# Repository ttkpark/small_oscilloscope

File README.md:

# small_oscilloscope
480x272 small-but-full oscilloscope

## stpes to go

### 아날로그 회로
 - 오실로스코프 회로 방식 파악 필요
 - DSO138의 회로 구성을 확인

### 오실로스코프 UI
 - 제어점과 보여줄 점을 파악 필요
 - `사용자의 입력은 무엇이 되어야 하는가`
 - `오실로스코프의 아날로그 유닛에 대한 제어 범위는?`
 - `어느 점을 보여주어야 하는가`

 - 트리거 인식 : 샘플 내에서 level지점 통과 지점을 지점 정중앙으로 둔다.
 - 샘플링 후 트리거 인식이 아니라, 샘플링 하면서 트리거 인식하면 트리거 지점이 정중앙되도록 샘플 수집하고 마무리.
 - 즉 샘플링 -> 트리거 x, 트리거 -> 샘플링 o

## 전원
- 상시 전원 공급 Source : VBAT=2.7 ~ 4.2
- BAT 충전       : 5V -> VBAT=4.2 (TP4056)
- 배터리 승압 회로 : VBAT -> 5V    (EA2208)
- 양전압 생성 회로 : VBAT -> 12V   (EA2208)
- 음전압 생성 회로 : 12V -> -12V   (LM2576)
- 백라이트 회로    : VBAT -> 24V   (EA2208)
- 강하 회로       : 5V -> 3.3V    (5V->3.3V 전압 강하 보드)

## 구성요소
- 본체 중앙처리장치
   - 구성 부품 : ESP32-PICO-D4
   - 인터페이스 : GPIO, SPI, I2C, ADC, UART, DAC 제공

- GPIO 확장 칩 : CH423
   - 구성 부품 : CH423
   - 인터페이스 : 본체 인터페이스 I2C 사용
               입출력 GPIO IO0-7, 출력 GPIO OC0-15 제공

- 아날로그 어레이
   - 구성 부품 : 전압 강하 OP-AMP, 감쇠율 조절 FET 및 릴레이, AC/DC 선택 릴레이, TRIG 생성기
   - 인터페이스 : GPIO 확장 칩 OC0,OC2-6,OC8-11 사용
                본체 인터페이스 GPIO(GPIO9-10), ADC(GPIO34, GPIO4), DAC(GPIO25, GPIO26) 사용
- 그래픽
   - 구성 부품 : FT800Q-T, 480x272 Monitor
   - 인터페이스 : 본체 인터페이스 SPI, 본체 GPIO (GPIO27:INT) 사용

- 조작부
   - 구성 부품 : 버튼, ROTARY Encoder, LED
   - 인터페이스 : GPIO 확장 칩 IO0-5, OC12-15 사용

- 연결부
   - 구성 부품 : CH340, BOOT Mode selecting MOSFET
   - 인터페이스 : 본체 인터페이스 UART, 본체 GPIO 부팅 핀(GPIO0, EN) 사용

- 충전부
   - 구성 부품 : 배터리 및 TP4056
   - 인터페이스 : GPIO 확장 칩 IO6-7 사용

- 전원부
   - 구성 부품 : 레퍼런스 전압을 나누는 Voltage Divisor
   - 인터페이스 : 본체 ADC 레퍼런스 전압 포트(GPIO35-39)

# 핀맵
|position|name|usage|
|----|----|----|
|UART(TX=GPIO1,RX=GPIO3)|CH340|Interface; uploading & debugging port|
|I2C(CK=GPIO21,DA=GPIO22)|CH423s|Interface; controlls the MOSFETs|
|SPI(SCK=GPIO18,MISO=GPIO19,MOSI=GPIO23,SS=GPIO5)|FT800Q-T|Interface; graphical controller, speaker enabled, DE Mode|
|GPIO27|/INT|LCD FT800Q-T Interrupt Pin|

|GPIO12|RE1B|Digital Input; Rotary Encoder 1(Volt Div/Pos) B|
|GPIO13|RE1A|Digital Input; Rotary Encoder 1(Volt Div/Pos) A|
|GPIO14|RE0B|Digital Input; Rotray Encoder 0(Time Div/Pos) B|
|GPIO15|RE0A|Digital Input; Rotray Encoder 0(Time Div/Pos) A|

|GPIO9|TRIG0|Digital Input, interrupt; open-drain, LOW if TRIG<ADC0|
|GPIO10|TRIG1|Digital Input, interrupt; open-drain, LOW if TRIG<ADC1|
|GPIO25|TRIG|Analog Output;  Trigger Output(same level with ADC0,1 pin)|
|GPIO34|ADC0|Analog Input;  Channel 0 input|
|GPIO4|ADC1|Analog Input;  Channel 1 input|
|GPIO26|TESTPIN|1kHz Signal Output pin|

|GPIO35|VREF3V3|Analog Reference Input;  3V3(VDD) ref, Vin=V33/2|
|GPIO36|VREFBAT|Analog Reference Input;  VBAT ref, Vin=VBAT/2|
|GPIO37|VREF5V |Analog Reference Input;  5V ref, Vin=V5/4.333|
|GPIO38|VREF12V|Analog Reference Input;  12V ref,Vin=V12/6.732|
|GPIO39|VREF135|Analog Reference Input;  2.7V ref, Vin=1.35V |

|CH423s-IO0|RE0P|Input; Rotary Encoder 0 Pushbutton(LOW Active)|
|CH423s-IO1|RE1P|Input; Rotary Encoder 1 Pushbutton(LOW Active)|
|CH423s-IO2|SW0|Input; button 0(LOW ACTIVE)|
|CH423s-IO3|SW1|Input; button 1(LOW ACTIVE)|
|CH423s-IO4|SW2|Input; button 2(LOW ACTIVE)|
|CH423s-IO5|SW3|Input; button 3(LOW ACTIVE)|
|CH423s-IO6|STDBY|Input; BATTERY 충전 완료면 HIGH|
|CH423s-IO7|CHRG|Input; BATTERY 충전 중이면 HIGH|
|CH423s-OC0|Q1|Output; Line 0 DC input analog switch|
|CH423s-OC1|BACKLIGHT|Output; LCD BACKLIGHT|
|CH423s-OC2|Q3|Output; Line 0 1차 1/10 감쇠|
|CH423s-OC3|Q4|Output; Line 0 1차 1/100 감쇠|
|CH423s-OC4|Q5|Output; Line 0 2차 1/2 감쇠|
|CH423s-OC5|Q6|Output; Line 0 2차 1/5 감쇠|
|CH423s-OC6|Q7|Output; Line 1 DC input analog switch|
|CH423s-OC7|-|Output; -|
|CH423s-OC8|Q9|Output; Line 1 1차 1/10 감쇠|
|CH423s-OC9|Q10|Output; Line 1 1차 1/100 감쇠|
|CH423s-OC10|Q11|Output; Line 1 2차 1/2 감쇠|
|CH423s-OC11|Q12|Output; Line 1 2차 1/5 감쇠|
|CH423s-OC12|LED0|Output; GP LED (Red)|
|CH423s-OC13|LED1|Output; GP LED (Green)|
|CH423s-OC14|LEDRE0|Output; Rotary Encoder 0 LED (Green)|
|CH423s-OC15|LEDRE1|Output; Rotary Encoder 1 LED (Green)|

# 하드웨어 연결 및 기능 구조

## 본체 중앙처리장치
   - 구성 부품 : ESP32-PICO-D4
   - 인터페이스 : GPIO, SPI, I2C, ADC, UART, DAC 제공

## GPIO 확장 칩 : CH423
   - 구성 부품 : CH423
   - 인터페이스 : 본체 인터페이스 I2C 사용
               입출력 GPIO IO0-7, 출력 GPIO OC0-15 제공
### 인터페이스 상세
|position|name|usage|
|----|----|----|
|I2C(CK=GPIO21,DA=GPIO22)|CH423s|Interface; controlls the MOSFETs|

### 설정
- 주소는 0x20이다. (7-bit addr)
analog_test_simple.c:84 esp_err_t test_ch423_circuit_simple(uint8_t *read_data) 의 테스트 함수에서 초기화 및 읽고 쓰는 법에 대해 쓰여 있다.

## 아날로그 어레이
- 구성 부품 : 전압 강하 OP-AMP, 감쇠율 조절 FET 및 릴레이, AC/DC 선택 릴레이, TRIG 생성기
- 인터페이스 : GPIO 확장 칩 OC0,OC2-6,OC8-11 사용
             본체 인터페이스 GPIO(GPIO9-10), ADC(GPIO34, GPIO4), DAC(GPIO25, GPIO26) 사용
### 인터페이스 상세
|position|name|usage|
|----|----|----|
|GPIO9|TRIG0|Digital Input, interrupt; open-drain, LOW if TRIG<ADC0|
|GPIO10|TRIG1|Digital Input, interrupt; open-drain, LOW if TRIG<ADC1|
|GPIO25|TRIG|Analog Output;  Trigger Output(same level with ADC0,1 pin)|
|GPIO34|ADC0|Analog Input;  Channel 0 input|
|GPIO35|ADC1|Analog Input;  Channel 1 input|
|GPIO26|TESTPIN|1kHz Signal Output pin|

|CH423s-OC0|Q1|Output; Line 0 DC input analog switch|
|CH423s-OC2|Q3|Output; Line 0 1차 1/10 감쇠|
|CH423s-OC3|Q4|Output; Line 0 1차 1/100 감쇠|
|CH423s-OC4|Q5|Output; Line 0 2차 1/2 감쇠|
|CH423s-OC5|Q6|Output; Line 0 2차 1/5 감쇠|
|CH423s-OC6|Q7|Output; Line 1 DC input analog switch|
|CH423s-OC8|Q9|Output; Line 1 1차 1/10 감쇠|
|CH423s-OC9|Q10|Output; Line 1 1차 1/100 감쇠|
|CH423s-OC10|Q11|Output; Line 1 2차 1/2 감쇠|
|CH423s-OC11|Q12|Output; Line 1 2차 1/5 감쇠|

### 프로브부터 ADC 포트까지 감쇠 회로 및 전압의 관계
- [출력] - [AC/DC 선택]  -   [1차 감쇠 회로] - [2차 감쇠 회로] - 레벨 쉬프터

### 감쇠율 조정 로직 : AC/DC 선택
|Q1/Q7|상태|
|--|--|
|0|DC입력(원본)|
|1|AC입력(AC성분만)|

### 감쇠율 조정 로직 : 1차 감쇠기
|Q3/Q9|Q4/Q10|상태|
|--|--|alpha_1|
|0|0|1|
|0|1|1/100|
|1|0|1/10|
|1|1|INVALD|
- V1 = alpha_1 * Vi

### 감쇠율 조정 로직 : 2차 감쇠기
|Q5/Q11|Q6/Q12|상태|
|--|--|alpha_2|
|0|0|1|
|0|1|1/5|
|1|0|1/2|
|1|1|INVALD|
- V2 = alpha_2 * V1

### 레벨 쉬프터 식
- Vadc = 8 * V2 + (V12/7.2)

### 출력과 ADC 입력의 관계
- Vadc = 8 * alpha_2 * alpha_1 * Vi + (V12 / 7.2)
- alpha_2,alpha_1은 1차 2차 감쇠값, Vadc는 adc포트 전압, Vi는 프로브 전압, V12는 12V레인 전압

### 트리거
- TRIG0, TRIG1 핀은 pull-up되어야 한다.
|TRIG>ADCn|TRIGn|
|--|--|
|true|HIGH|
|false|LOW|

## 그래픽
   - 구성 부품 : FT800Q-T, 480x272 Monitor
   - 인터페이스 : 본체 인터페이스 SPI, 본체 GPIO (GPIO27:INT) 사용

|position|name|usage|
|----|----|----|
|SPI(SCK=GPIO18,MISO=GPIO19,MOSI=GPIO23,SS=GPIO5)|FT800Q-T|Interface; graphical controller, speaker enabled, DE Mode|
|GPIO27|/INT|LCD FT800Q-T Interrupt Pin|
|CH423s-OC1|BACKLIGHT|Output; LCD BACKLIGHT|
### 사용법
- 사전에 반드시 **CH423이 먼저 초기화되고, BACKLIGHT 핀을 LOW 해야 한다.**
- 아래 코드처럼 초기화하고, 그림을 그리고 효과음을 낸다.
```c
   // FT800 초기화
    if (!initFT800()) {
        ESP_LOGI(TAG, "FT800 test passed");
    } else {
        ESP_LOGE(TAG, "FT800 test failed");
    }
    vTaskDelay(pdMS_TO_TICKS(1000));

    spi_speedup();
    
    // FT800 사용
	 clrscr();
    while(1){
		static uint32_t frames = 0;
        uint32_t frames_old = frames;
        frames = HOST_MEM_RD32(REG_FRAMES);
        if(frames_old != frames)
        {
            lcd_start_screen(frames);
            //ESP_LOGI(TAG, "FRAMES: %ld", frames);

            char str[100];
            sprintf(str, "FRAMES: %ld", frames);
            cmd(COLOR_RGB(0xDE,0xDE,0xDE));
            cmd_text(10,230, 27,0, str);
            
            memset(str, 0, sizeof(str));
            sprintf(str, "GPIO12 = %d", gpio_get_level(12));
            cmd(COLOR_RGB(0xDE,0xDE,0xDE));
            cmd_text(470,230, 26,OPT_RIGHTX, str);

            cmd(DISPLAY());
            cmd(CMD_SWAP);	
        }
        vTaskDelay(pdMS_TO_TICKS(1));
    }

    // 소리 내기
   HOST_MEM_WR8(REG_VOL_SOUND, 0xFF);      	
   switch((frames%180)/60){
      case 0:
         HOST_MEM_WR16(REG_SOUND, 0x50);     
         break;
      case 1:
         HOST_MEM_WR16(REG_SOUND, 0x51);
         break;
      case 2:
         HOST_MEM_WR16(REG_SOUND, 0x56);
         break;
   }
   HOST_MEM_WR8(REG_PLAY, 1); 
   
```

## 조작부
   - 구성 부품 : 버튼, ROTARY Encoder, LED
   - 인터페이스 : GPIO 확장 칩 IO0-5, OC12-15 사용

|position|name|usage|
|----|----|----|
|GPIO12|RE1B|Digital Input; Rotary Encoder 1(Volt Div/Pos) B|
|GPIO13|RE1A|Digital Input; Rotary Encoder 1(Volt Div/Pos) A|
|GPIO14|RE0B|Digital Input; Rotray Encoder 0(Time Div/Pos) B|
|GPIO15|RE0A|Digital Input; Rotray Encoder 0(Time Div/Pos) A|
|CH423s-IO0|RE0P|Input; Rotary Encoder 0 Pushbutton(LOW Active)|
|CH423s-IO1|RE1P|Input; Rotary Encoder 1 Pushbutton(LOW Active)|
|CH423s-IO2|SW0|Input; button 0(LOW ACTIVE)|
|CH423s-IO3|SW1|Input; button 1(LOW ACTIVE)|
|CH423s-IO4|SW2|Input; button 2(LOW ACTIVE)|
|CH423s-IO5|SW3|Input; button 3(LOW ACTIVE)|
|CH423s-OC12|LED0|Output; GP LED (Red)|
|CH423s-OC13|LED1|Output; GP LED (Green)|
|CH423s-OC14|LEDRE0|Output; Rotary Encoder 0 LED (Green)|
|CH423s-OC15|LEDRE1|Output; Rotary Encoder 1 LED (Green)|

- 로터리 스위치의 움직임 방향, 버튼의 눌림을 알 수 있고, LED 4개로 확인할 수 있다.

## 연결부
   - 구성 부품 : CH340, BOOT Mode selecting MOSFET
   - 인터페이스 : 본체 인터페이스 UART, 본체 GPIO 부팅 핀(GPIO0, EN) 사용

|position|name|usage|
|----|----|----|
|UART(TX=GPIO1,RX=GPIO3)|CH340|Interface; uploading & debugging port|

## 충전부
   - 구성 부품 : 배터리 및 TP4056
   - 인터페이스 : GPIO 확장 칩 IO6-7 사용
|position|name|usage|
|----|----|----|
|CH423s-IO6|STDBY|Input; BATTERY 충전 완료면 HIGH|
|CH423s-IO7|CHRG|Input; BATTERY 충전 중이면 HIGH|

### 충전 상태 설명
|STDBY|CHRG|상태|
|--|--|--|
|LOW |LOW |외부전원 분리됨|
|LOW |HIGH|충전 중|
|HIGH|LOW |충전 완료|
|HIGH|HIGH|INVALID, 아마도 충전중|

## 전원부
   - 구성 부품 : 레퍼런스 전압을 나누는 Voltage Divisor
   - 인터페이스 : 본체 ADC 레퍼런스 전압 포트(GPIO35-39)

### 인터페이스 상세
|position|name|usage|
|----|----|----|
|GPIO36|VREFBAT|Analog Reference Input;  VBAT ref, Vin=VBAT/2|
|GPIO37|VREF5V |Analog Reference Input;  5V ref, Vin=V5/4.333|
|GPIO38|VREF12V|Analog Reference Input;  12V ref,Vin=V12/6.732|
|GPIO39|VREF135|Analog Reference Input;  2.7V ref, Vin=1.35V |

### 사용법
- VREF135 포트는 제너 다이오드로 연결된 거의 신뢰성 있는 전압이다. 이것을 기준으로 ADC Max Volt를 역산한다.(=VDD)
- VREFBAT의 입력을 전압으로 변환해 배터리 전압을 추출한다.
- VREF5V, 12V의 ADC입력을 전압으로 변환해 각 레인의 전압을 추출한다.
- VREF3V3은 VDD로 계산되지만, 검증용으로 예비로 전압을 추출한다.

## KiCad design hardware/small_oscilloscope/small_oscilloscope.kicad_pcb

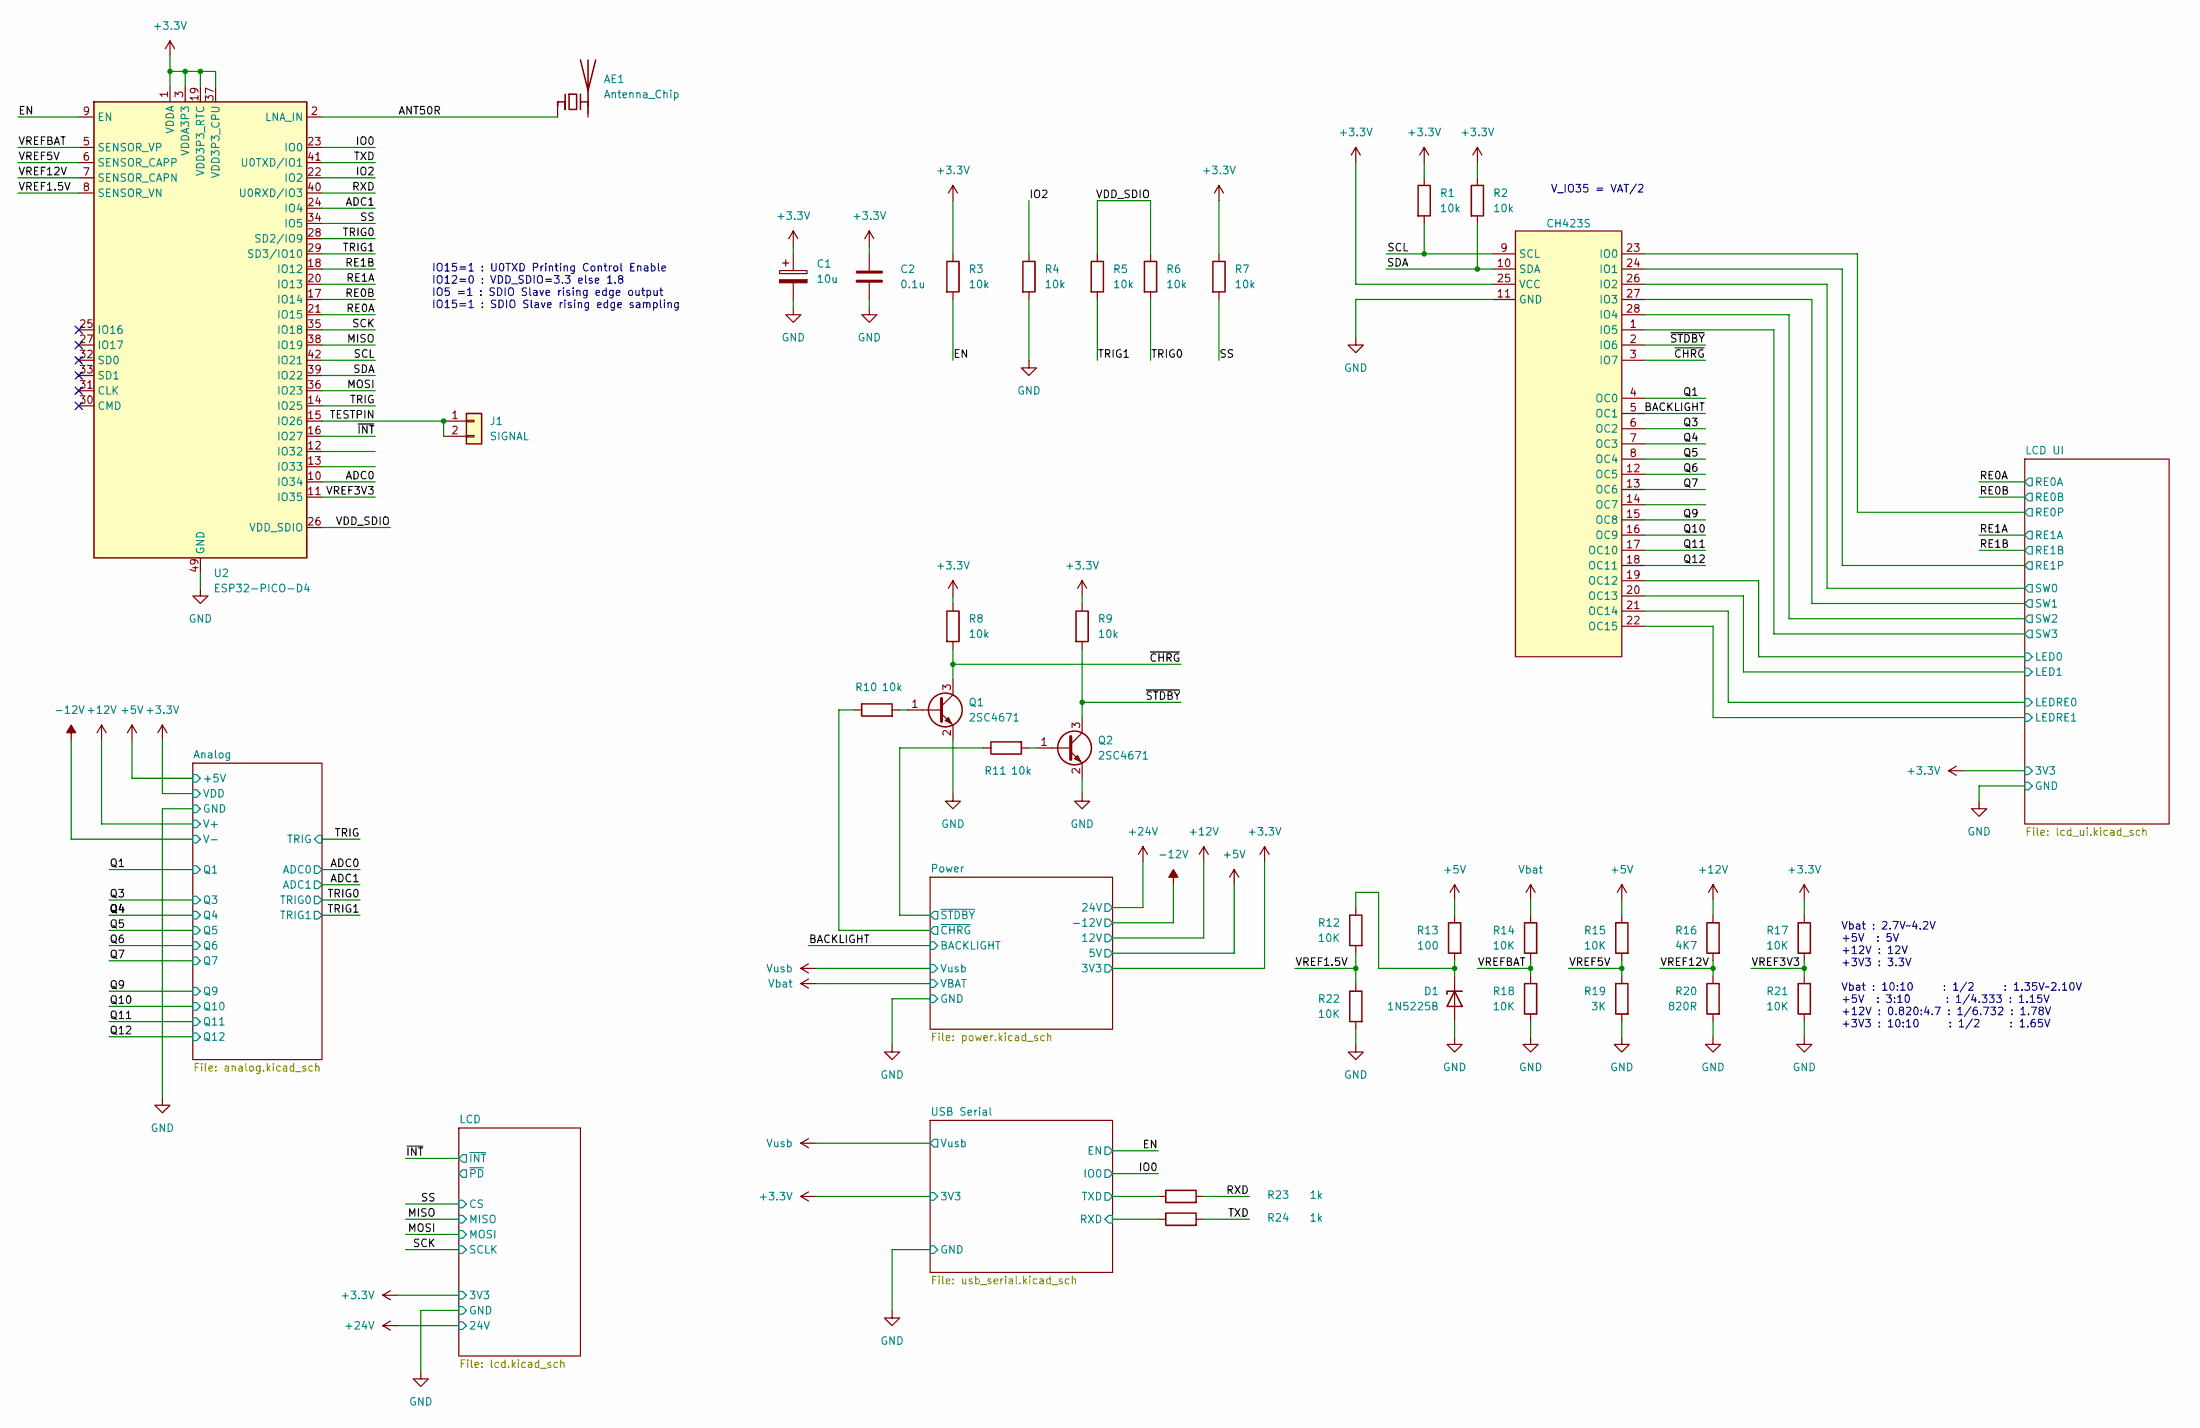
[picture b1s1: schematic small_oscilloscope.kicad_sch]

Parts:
AE1: Antenna_Chip; L_1206_3216Metric_Pad1.22x1.90mm_HandSolder
C1: 10u; CP_Elec_5x5.3
C2: 0.1u; C_0402_1005Metric_Pad0.74x0.62mm_HandSolder
D1: 1N5225B; D_A-405_P7.62mm_Horizontal
J1: SIGNAL; PinSocket_1x02_P2.54mm_Vertical
Q1, Q2: 2SC4671; SOT-523
R1, R2, R3, R4, R5, R6, R7, R8, R9, R10, R11: 10k; R_0402_1005Metric_Pad0.72x0.64mm_HandSolder
R12, R14, R15, R17, R18, R21, R22: 10K; R_0402_1005Metric_Pad0.72x0.64mm_HandSolder
R13: 100; R_0603_1608Metric_Pad0.98x0.95mm_HandSolder
R16: 4K7; R_0402_1005Metric_Pad0.72x0.64mm_HandSolder
R19: 3K; R_0402_1005Metric_Pad0.72x0.64mm_HandSolder
R20: 820R; R_0402_1005Metric_Pad0.72x0.64mm_HandSolder
R23, R24: 1k; R_0603_1608Metric_Pad0.98x0.95mm_HandSolder
U1: CH423S; SOP-28_8.4x18.16mm_P1.27mm
U2: ESP32-PICO-D4; QFN-48-1EP_7x7mm_P0.5mm_EP5.3x5.3mm

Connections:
+3.3V: C1.1, C2.1, R1.1, R2.1, R3.1, R7.1, R8.1, R9.1, R17.1, U1.25 (VCC), U2.1 (VDDA), U2.3 (VDDA3P3), U2.4 (VDDA3P3), U2.19 (VDD3P3_RTC), U2.37 (VDD3P3_CPU), U2.43 (VDDA), U2.46 (VDDA); also elsewhere on the board
+5V: R13.1, R15.1; also elsewhere on the board
+12V: R16.1; also elsewhere on the board
/ADC0: U2.10 (IO34); also elsewhere on the board
/ADC1: U2.24 (IO4); also elsewhere on the board
/ANT50R: AE1.1 (FEED), U2.2 (LNA_IN)
/BACKLIGHT: U1.5 (OC1); also elsewhere on the board
/EN: R3.2, U2.9 (EN); also elsewhere on the board
/IO0: U2.23 (IO0); also elsewhere on the board
/IO2: R4.1, U2.22 (IO2)
/LCD UI/LED0: U1.19 (OC12); also elsewhere on the board
/LCD UI/LED1: U1.20 (OC13); also elsewhere on the board
/LCD UI/LEDRE0: U1.21 (OC14); also elsewhere on the board
/LCD UI/LEDRE1: U1.22 (OC15); also elsewhere on the board
/LCD UI/RE0P: U1.23 (IO0); also elsewhere on the board
/LCD UI/RE1P: U1.24 (IO1); also elsewhere on the board
/LCD UI/SW0: U1.26 (IO2); also elsewhere on the board
/LCD UI/SW1: U1.27 (IO3); also elsewhere on the board
/LCD UI/SW2: U1.28 (IO4); also elsewhere on the board
/LCD UI/SW3: U1.1 (IO5); also elsewhere on the board
/MISO: U2.38 (IO19); also elsewhere on the board
/MOSI: U2.36 (IO23); also elsewhere on the board
/Power/~CHRG: R10.1; also elsewhere on the board
/Power/~STDBY: R11.1; also elsewhere on the board
/Q1: U1.4 (OC0); also elsewhere on the board
/Q3: U1.6 (OC2); also elsewhere on the board
/Q4: U1.7 (OC3); also elsewhere on the board
/Q5: U1.8 (OC4); also elsewhere on the board
/Q6: U1.12 (OC5); also elsewhere on the board
/Q7: U1.13 (OC6); also elsewhere on the board
/Q9: U1.15 (OC8); also elsewhere on the board
/Q10: U1.16 (OC9); also elsewhere on the board
/Q11: U1.17 (OC10); also elsewhere on the board
/Q12: U1.18 (OC11); also elsewhere on the board
/RE0A: U2.21 (IO15); also elsewhere on the board
/RE0B: U2.17 (IO14); also elsewhere on the board
/RE1A: U2.20 (IO13); also elsewhere on the board
/RE1B: U2.18 (IO12); also elsewhere on the board
/RXD: R23.2, U2.40 (U0RXD/IO3)
/SCK: U2.35 (IO18); also elsewhere on the board
/SCL: R1.2, U1.9 (SCL), U2.42 (IO21)
/SDA: R2.2, U1.10 (SDA), U2.39 (IO22)
/SS: R7.2, U2.34 (IO5); also elsewhere on the board
/TESTPIN: J1.1, J1.2, U2.15 (IO26)
/TRIG0: R6.2, U2.28 (SD2/IO9); also elsewhere on the board
/TRIG1: R5.2, U2.29 (SD3/IO10); also elsewhere on the board
/TXD: R24.2, U2.41 (U0TXD/IO1)
/USB Serial/RXD: R24.1; also elsewhere on the board
/USB Serial/TXD: R23.1; also elsewhere on the board
/VDD_SDIO: R5.1, R6.1, U2.26 (VDD_SDIO)
/VREF1.5V: R12.2, R22.1, U2.8 (SENSOR_VN)
/VREF3V3: R17.2, R21.1, U2.11 (IO35)
/VREF5V: R15.2, R19.1, U2.6 (SENSOR_CAPP)
/VREF12V: R16.2, R20.1, U2.7 (SENSOR_CAPN)
/VREFBAT: R14.2, R18.1, U2.5 (SENSOR_VP)
/~CHRG: Q1.3 (C), R8.2, U1.3 (IO7)
/~INT: U2.16 (IO27); also elsewhere on the board
/~STDBY: Q2.3 (C), R9.2, U1.2 (IO6)
GND: C1.2, C2.2, D1.2 (A), Q1.2 (E), Q2.2 (E), R4.2, R18.2, R19.2, R20.2, R21.2, R22.2, U1.11 (GND), U2.49 (GND); also elsewhere on the board
unnamed: D1.1 (K), R12.1, R13.2
unnamed: Q1.1 (B), R10.2
unnamed: Q2.1 (B), R11.2
TRIG: U2.14 (IO25); also elsewhere on the board
Vbat: R14.1; also elsewhere on the board

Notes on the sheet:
IO15=1 : U0TXD Printing Control Enable IO12=0 : VDD_SDIO=3.3 else 1.8 IO5 =1 : SDIO Slave rising edge output IO15=1 : SDIO Slave rising edge sampling
V_IO35 = VAT/2
Vbat : 2.7V~4.2V +5V : 5V +12V : 12V +3V3 : 3.3V Vbat : 10:10 : 1/2 : 1.35V~2.10V +5V : 3:10 : 1/4.333 : 1.15V +12V : 0.820:4.7 : 1/6.732 : 1.78V +3V3 : 10:10 : 1/2 : 1.65V

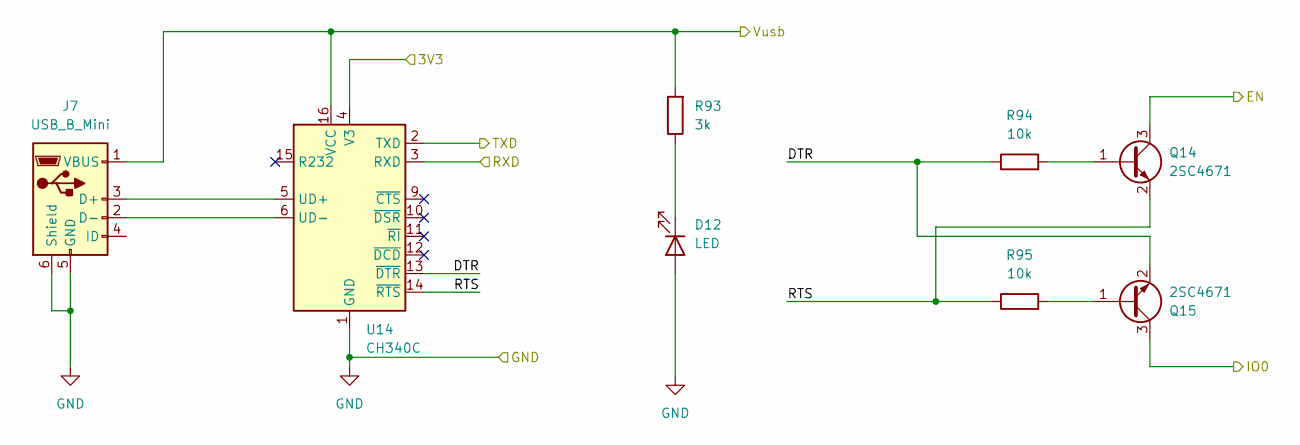
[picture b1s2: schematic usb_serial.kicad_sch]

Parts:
D12: LED; LED_D3.0mm
J7: USB_B_Mini; USB_Mini-B_Lumberg_2486_01_Horizontal
Q14, Q15: 2SC4671; SOT-523
R93: 3k; R_0402_1005Metric_Pad0.72x0.64mm_HandSolder
R94, R95: 10k; R_0402_1005Metric_Pad0.72x0.64mm_HandSolder
U14: CH340C; SOIC-16_3.9x9.9mm_P1.27mm

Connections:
+3.3V: U14.4 (V3); also elsewhere on the board
/EN: Q14.3 (C); also elsewhere on the board
/IO0: Q15.3 (C); also elsewhere on the board
/USB Serial/DTR: Q15.2 (E), R94.1, U14.13 (~DTR)
/USB Serial/RTS: Q14.2 (E), R95.1, U14.14 (~RTS)
/USB Serial/RXD: U14.3 (RXD); also elsewhere on the board
/USB Serial/TXD: U14.2 (TXD); also elsewhere on the board
GND: D12.2 (A), J7.5 (GND), J7.6 (Shield), U14.1 (GND); also elsewhere on the board
unnamed: D12.1 (K), R93.1
unnamed: J7.3 (D+), U14.5 (UD+)
unnamed: J7.2 (D-), U14.6 (UD-)
unnamed: Q14.1 (B), R94.2
unnamed: Q15.1 (B), R95.2
Vusb: J7.1 (VBUS), R93.2, U14.16 (VCC); also elsewhere on the board

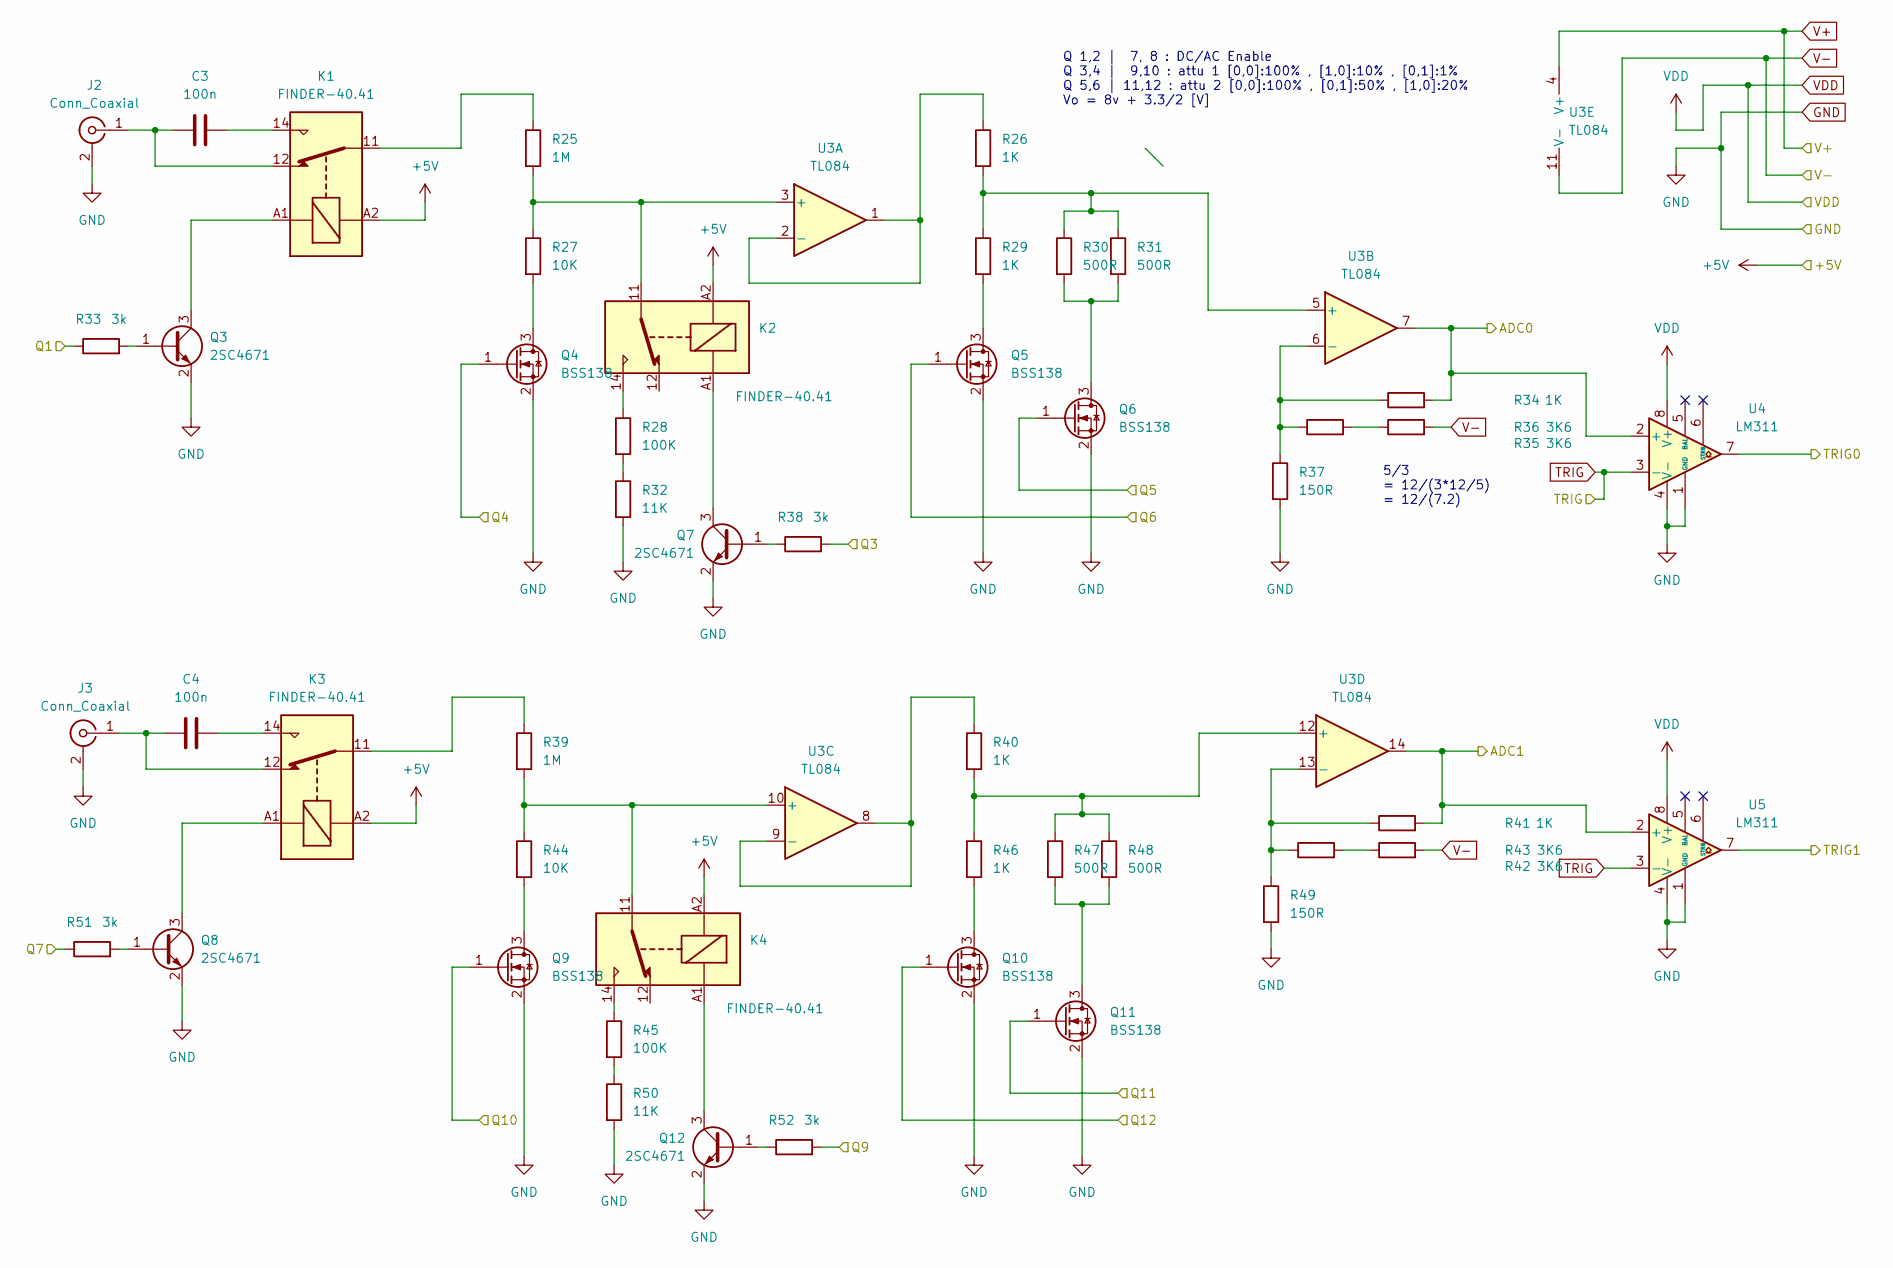
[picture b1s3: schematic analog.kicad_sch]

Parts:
C3, C4: 100n; C_0402_1005Metric_Pad0.74x0.62mm_HandSolder
J2, J3: Conn_Coaxial; BNC_Amphenol_B6252HB-NPP3G-50_Horizontal
K1, K2, K3, K4: FINDER-40.41; Relay_SPDT_Finder_40.41
Q3, Q7, Q8, Q12: 2SC4671; SOT-523
Q4, Q5, Q6, Q9, Q10, Q11: BSS138; SOT-23_Handsoldering
R25, R39: 1M; R_Axial_DIN0207_L6.3mm_D2.5mm_P10.16mm_Horizontal
R26, R29, R34, R40, R41, R46: 1K; R_Axial_DIN0207_L6.3mm_D2.5mm_P10.16mm_Horizontal
R27, R44: 10K; R_Axial_DIN0207_L6.3mm_D2.5mm_P10.16mm_Horizontal
R28, R45: 100K; R_Axial_DIN0207_L6.3mm_D2.5mm_P10.16mm_Horizontal
R30, R31, R47, R48: 500R; R_Axial_DIN0207_L6.3mm_D2.5mm_P10.16mm_Horizontal
R32, R50: 11K; R_Axial_DIN0207_L6.3mm_D2.5mm_P10.16mm_Horizontal
R33, R38, R51, R52: 3k; R_0402_1005Metric_Pad0.72x0.64mm_HandSolder
R35, R36, R42, R43: 3K6; R_Axial_DIN0207_L6.3mm_D2.5mm_P10.16mm_Horizontal
R37, R49: 150R; R_Axial_DIN0207_L6.3mm_D2.5mm_P10.16mm_Horizontal
U3: TL084; SOIC-14_3.9x8.7mm_P1.27mm
U4, U5: LM311; DIP-8_W7.62mm_LongPads

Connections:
+3.3V: U4.8 (V+), U5.8 (V+); also elsewhere on the board
+5V: K1.A2, K2.A2, K3.A2, K4.A2; also elsewhere on the board
+12V: U3.4 (V+); also elsewhere on the board
-12V: R36.2, R43.2, U3.11 (V-); also elsewhere on the board
/ADC0: R34.2, U3.7, U4.2 (+); also elsewhere on the board
/ADC1: R41.2, U3.14, U5.2 (+); also elsewhere on the board
/Q1: R33.1; also elsewhere on the board
/Q3: R38.2; also elsewhere on the board
/Q4: Q4.1 (G); also elsewhere on the board
/Q5: Q6.1 (G); also elsewhere on the board
/Q6: Q5.1 (G); also elsewhere on the board
/Q7: R51.1; also elsewhere on the board
/Q9: R52.2; also elsewhere on the board
/Q10: Q9.1 (G); also elsewhere on the board
/Q11: Q11.1 (G); also elsewhere on the board
/Q12: Q10.1 (G); also elsewhere on the board
/TRIG0: U4.7; also elsewhere on the board
/TRIG1: U5.7; also elsewhere on the board
GND: J2.2 (Ext), J3.2 (Ext), Q3.2 (E), Q4.2 (S), Q5.2 (S), Q6.2 (S), Q7.2 (E), Q8.2 (E), Q9.2 (S), Q10.2 (S), Q11.2 (S), Q12.2 (E), R32.2, R37.2, R49.2, R50.2, U4.1 (GND), U4.4 (V-), U5.1 (GND), U5.4 (V-); also elsewhere on the board
unnamed: C3.2, K1.14
unnamed: C4.2, K3.14
unnamed: C3.1, J2.1 (In), K1.12
unnamed: C4.1, J3.1 (In), K3.12
unnamed: K1.11, R25.1
unnamed: K2.14, R28.1
unnamed: K3.11, R39.1
unnamed: K4.14, R45.1
unnamed: Q3.1 (B), R33.2
unnamed: K1.A1, Q3.3 (C)
unnamed: Q4.3 (D), R27.2
unnamed: Q5.3 (D), R29.2
unnamed: Q6.3 (D), R30.2, R31.2
unnamed: Q7.1 (B), R38.1
unnamed: K2.A1, Q7.3 (C)
unnamed: Q8.1 (B), R51.2
unnamed: K3.A1, Q8.3 (C)
unnamed: Q9.3 (D), R44.2
unnamed: Q10.3 (D), R46.2
unnamed: Q11.3 (D), R47.2, R48.2
unnamed: Q12.1 (B), R52.1
unnamed: K4.A1, Q12.3 (C)
unnamed: R28.2, R32.1
unnamed: R35.2, R36.1
unnamed: R42.2, R43.1
unnamed: R45.2, R50.1
unnamed: K2.11, R25.2, R27.1, U3.3 (+)
unnamed: R26.1, U3.1, U3.2 (-)
unnamed: R26.2, R29.1, R30.1, R31.1, U3.5 (+)
unnamed: R34.1, R35.1, R37.1, U3.6 (-)
unnamed: K4.11, R39.2, R44.1, U3.10 (+)
unnamed: R40.1, U3.8, U3.9 (-)
unnamed: R40.2, R46.1, R47.1, R48.1, U3.12 (+)
unnamed: R41.1, R42.1, R49.1, U3.13 (-)
TRIG: U4.3 (-), U5.3 (-); also elsewhere on the board

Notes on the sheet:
Q 1,2 | 7, 8 : DC/AC Enable Q 3,4 | 9,10 : attu 1 [0,0]:100% , [1,0]:10% , [0,1]:1% Q 5,6 | 11,12 : attu 2 [0,0]:100% , [0,1]:50% , [1,0]:20% Vo = 8v + 3.3/2 [V]
5/3 = 12/(3*12/5) = 12/(7.2)

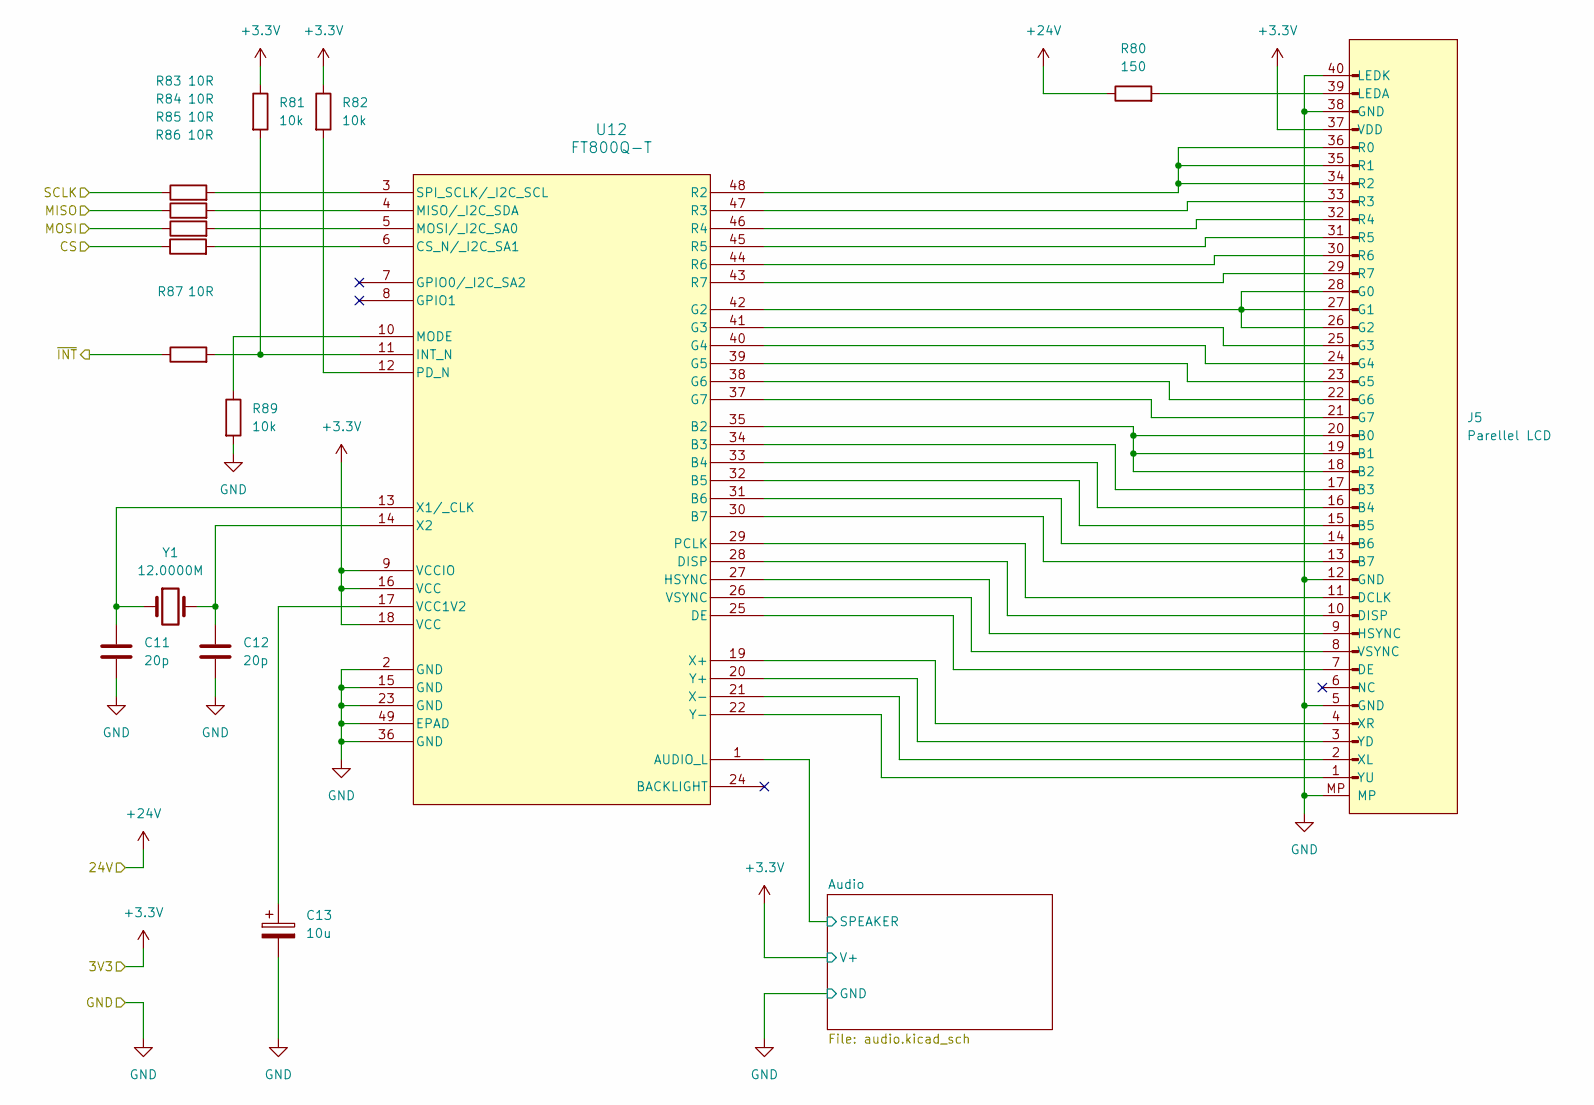
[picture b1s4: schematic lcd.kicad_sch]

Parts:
C11, C12: 20p; C_0402_1005Metric_Pad0.74x0.62mm_HandSolder
C13: 10u; CP_Elec_5x5.3
J5: Parellel LCD; TE_4-1734839-0_1x40-1MP_P0.5mm_Horizontal
R80: 150; R_0402_1005Metric_Pad0.72x0.64mm_HandSolder
R81, R82, R89: 10k; R_0402_1005Metric_Pad0.72x0.64mm_HandSolder
R83, R84, R85, R86, R87: 10R; R_1206_3216Metric_Pad1.30x1.75mm_HandSolder
U12: FT800Q-T; VQFN-48-1EP_7x7mm_P0.5mm_EP4.1x4.1mm
Y1: 12.0000M; Crystal_HC49-4H_Vertical

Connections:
+3.3V: J5.37 (VDD), R81.1, R82.1, U12.9 (VCCIO), U12.16 (VCC), U12.18 (VCC); also elsewhere on the board
+24V: R80.1; also elsewhere on the board
/LCD/Audio/SPEAKER: U12.1 (AUDIO_L); also elsewhere on the board
/MISO: R84.1; also elsewhere on the board
/MOSI: R85.1; also elsewhere on the board
/SCK: R83.1; also elsewhere on the board
/SS: R86.1; also elsewhere on the board
/~INT: R87.1; also elsewhere on the board
GND: C11.2, C12.2, C13.2, J5.5 (GND), J5.12 (GND), J5.38 (GND), J5.40 (LEDK), J5.MP, R89.2, U12.2 (GND), U12.15 (GND), U12.23 (GND), U12.36 (GND), U12.49 (EPAD); also elsewhere on the board
unnamed: J5.18 (B2), J5.19 (B1), J5.20 (B0), U12.35 (B2)
unnamed: J5.17 (B3), U12.34 (B3)
unnamed: J5.16 (B4), U12.33 (B4)
unnamed: J5.15 (B5), U12.32 (B5)
unnamed: J5.14 (B6), U12.31 (B6)
unnamed: J5.13 (B7), U12.30 (B7)
unnamed: J5.11 (DCLK), U12.29 (PCLK)
unnamed: J5.7 (DE), U12.25 (DE)
unnamed: J5.10 (DISP), U12.28 (DISP)
unnamed: J5.26 (G2), J5.27 (G1), J5.28 (G0), U12.42 (G2)
unnamed: J5.25 (G3), U12.41 (G3)
unnamed: J5.24 (G4), U12.40 (G4)
unnamed: J5.23 (G5), U12.39 (G5)
unnamed: J5.22 (G6), U12.38 (G6)
unnamed: J5.21 (G7), U12.37 (G7)
unnamed: J5.9 (HSYNC), U12.27 (HSYNC)
unnamed: J5.39 (LEDA), R80.2
unnamed: J5.34 (R2), J5.35 (R1), J5.36 (R0), U12.48 (R2)
unnamed: J5.33 (R3), U12.47 (R3)
unnamed: J5.32 (R4), U12.46 (R4)
unnamed: J5.31 (R5), U12.45 (R5)
unnamed: J5.30 (R6), U12.44 (R6)
unnamed: J5.29 (R7), U12.43 (R7)
unnamed: J5.8 (VSYNC), U12.26 (VSYNC)
unnamed: J5.2 (XL), U12.21 (X-)
unnamed: J5.4 (XR), U12.19 (X+)
unnamed: J5.3 (YD), U12.20 (Y+)
unnamed: J5.1 (YU), U12.22 (Y-)
unnamed: R86.2, U12.6 (CS_N/_I2C_SA1)
unnamed: R81.2, R87.2, U12.11 (INT_N)
unnamed: R84.2, U12.4 (MISO/_I2C_SDA)
unnamed: R89.1, U12.10 (MODE)
unnamed: R85.2, U12.5 (MOSI/_I2C_SA0)
unnamed: R82.2, U12.12 (PD_N)
unnamed: R83.2, U12.3 (SPI_SCLK/_I2C_SCL)
unnamed: C13.1, U12.17 (VCC1V2)
unnamed: C11.1, U12.13 (X1/_CLK), Y1.1
unnamed: C12.1, U12.14 (X2), Y1.2

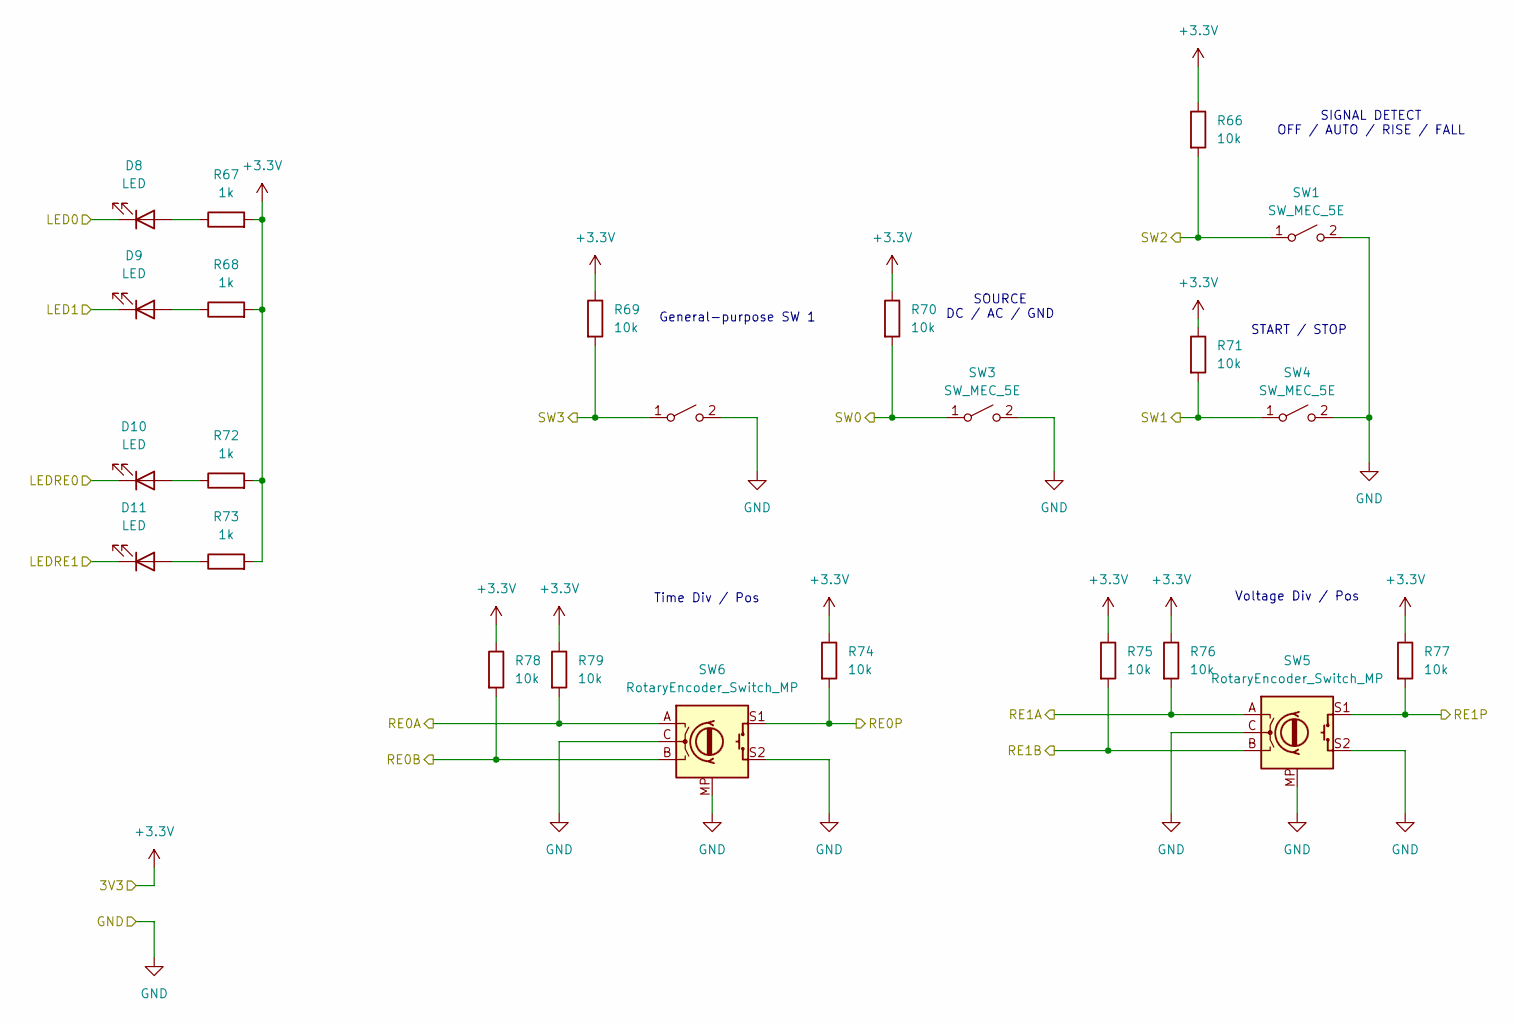
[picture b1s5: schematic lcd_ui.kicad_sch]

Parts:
D8, D9, D10, D11: LED; LED_D3.0mm
R66, R69, R70, R71, R74, R75, R76, R77, R78, R79: 10k; R_0402_1005Metric_Pad0.72x0.64mm_HandSolder
R67, R68, R72, R73: 1k; R_0603_1608Metric_Pad0.98x0.95mm_HandSolder
SW1, SW2, SW3, SW4: SW_MEC_5E; SW_PUSH_6mm_H4.3mm
SW5, SW6: RotaryEncoder_Switch_MP; RotaryEncoder_Alps_EC11E-Switch_Vertical_H20mm_MountingHoles

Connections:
+3.3V: R66.1, R67.2, R68.2, R69.1, R70.1, R71.1, R72.2, R73.2, R74.1, R75.1, R76.1, R77.1, R78.1, R79.1; also elsewhere on the board
/LCD UI/LED0: D8.1 (K); also elsewhere on the board
/LCD UI/LED1: D9.1 (K); also elsewhere on the board
/LCD UI/LEDRE0: D10.1 (K); also elsewhere on the board
/LCD UI/LEDRE1: D11.1 (K); also elsewhere on the board
/LCD UI/RE0P: R74.2, SW6.S1; also elsewhere on the board
/LCD UI/RE1P: R77.2, SW5.S1; also elsewhere on the board
/LCD UI/SW0: R70.2, SW3.1 (A); also elsewhere on the board
/LCD UI/SW1: R71.2, SW4.1 (A); also elsewhere on the board
/LCD UI/SW2: R66.2, SW1.1 (A); also elsewhere on the board
/LCD UI/SW3: R69.2, SW2.1 (A); also elsewhere on the board
/RE0A: R79.2, SW6.A; also elsewhere on the board
/RE0B: R78.2, SW6.B; also elsewhere on the board
/RE1A: R76.2, SW5.A; also elsewhere on the board
/RE1B: R75.2, SW5.B; also elsewhere on the board
GND: SW1.2 (B), SW2.2 (B), SW3.2 (B), SW4.2 (B), SW5.C, SW5.MP, SW5.S2, SW6.C, SW6.MP, SW6.S2; also elsewhere on the board
unnamed: D8.2 (A), R67.1
unnamed: D9.2 (A), R68.1
unnamed: D10.2 (A), R72.1
unnamed: D11.2 (A), R73.1

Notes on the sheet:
SIGNAL DETECT OFF / AUTO / RISE / FALL
General-purpose SW 1
START / STOP
SOURCE DC / AC / GND
Voltage Div / Pos
Time Div / Pos
